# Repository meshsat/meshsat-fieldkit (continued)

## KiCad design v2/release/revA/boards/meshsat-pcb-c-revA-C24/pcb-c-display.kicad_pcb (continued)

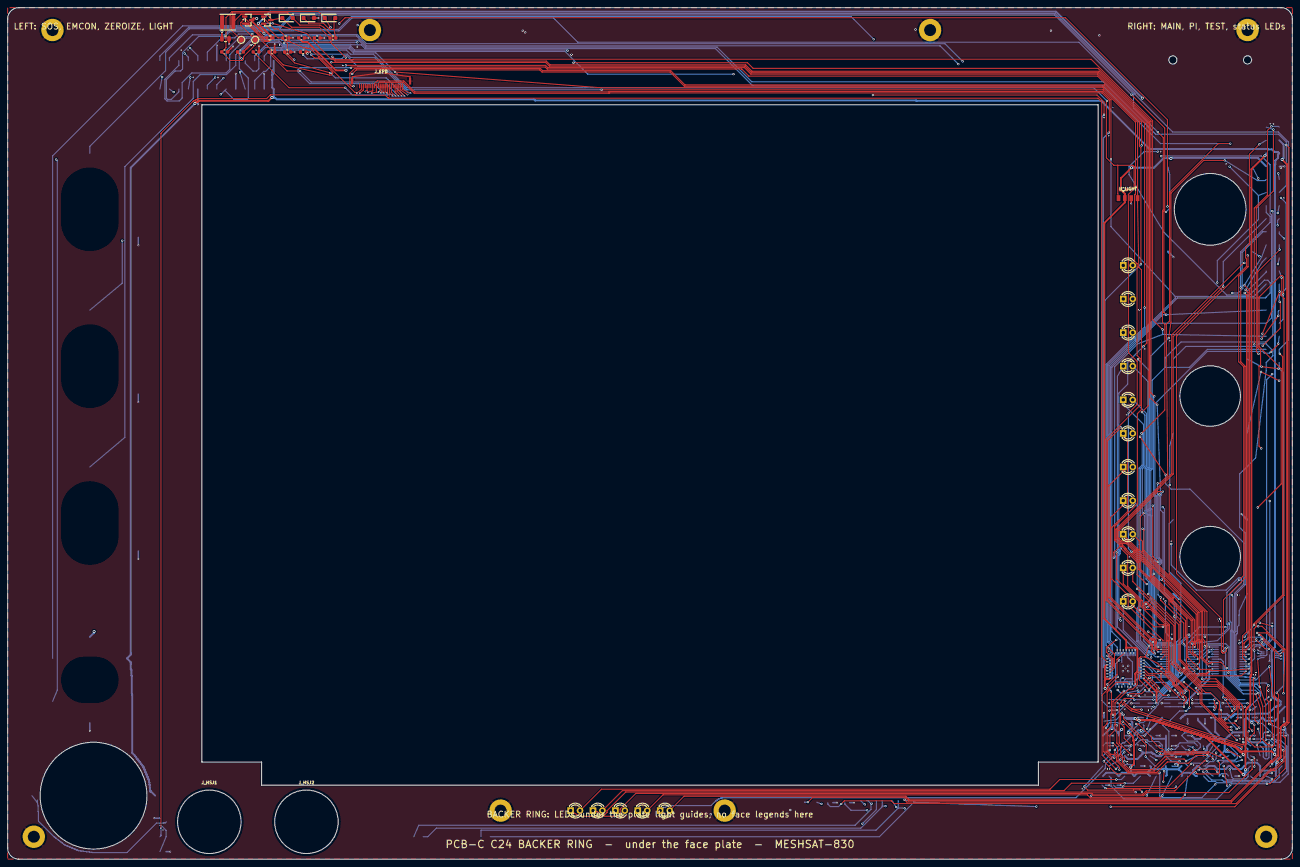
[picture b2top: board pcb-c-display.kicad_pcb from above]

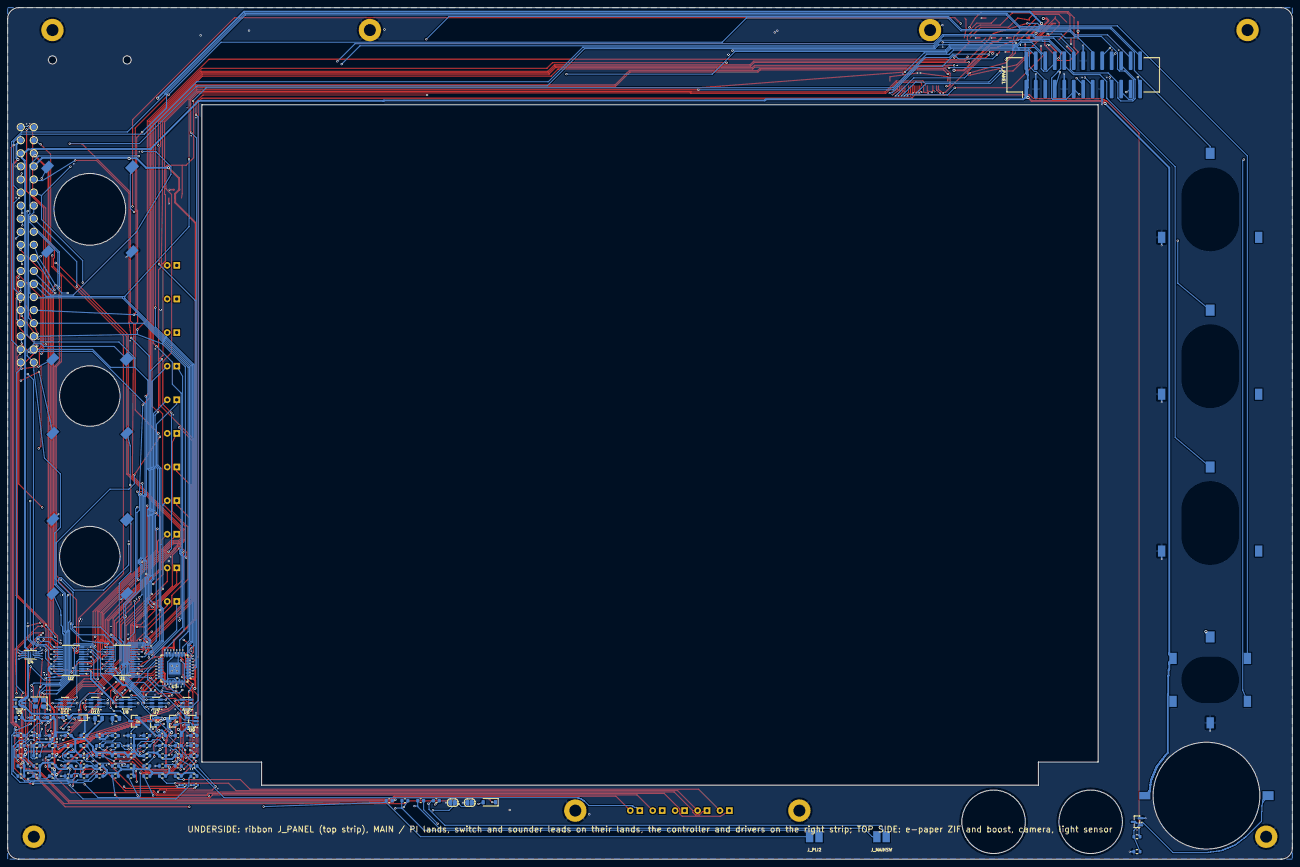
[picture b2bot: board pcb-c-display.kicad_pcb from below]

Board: 4 copper layers, 344.0 x 228.0 mm, 194 parts (135 on the bottom side), 133 nets.

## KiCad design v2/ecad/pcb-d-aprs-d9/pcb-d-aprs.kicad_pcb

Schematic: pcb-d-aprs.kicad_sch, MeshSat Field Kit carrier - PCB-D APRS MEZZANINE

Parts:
C1, C2, C5: 47u 6.3V X5R 1210; C_1210_3225Metric
C3, C9, C17, C24, C25, C33, C40: 10u; C_0805_2012Metric
C4, C6, C11, C15, C16, C39, C49, C50, C51, C52, C53, C54, C55, C56, C57, C62, C63: 100n; C_0603_1608Metric
C7, C8, C12, C18, C19, C20, C21, C22, C23, C28, C29, C30, C31, C32, C34, C35, C36, C37, C38, C41, C42, C46, C47, C48: 1u; C_0603_1608Metric
C10: 4.7u; C_0805_2012Metric
C13, C14: 27p NP0; C_0402_1005Metric
C26, C27: 18p NP0; C_0402_1005Metric
C43: 100p NP0; C_0402_1005Metric
C44, C45: 1n NP0; C_0402_1005Metric
C58, C60: 22p 500V NP0 1206; C_1206_3216Metric
C59: 39p 500V NP0 1206; C_1206_3216Metric
C61: 4.7n; C_0402_1005Metric
D1: SMBJ5.0A; D_SMB
D2: 1N4148W coil flyback; D_SOD-123
FB1: 600R 2A ferrite (the exciter's 1 A transmit pulse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; L_0805_2012Metric
JP1: electret bias headset 1 (close for an electret mi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; SolderJumper-2_P1.3mm_Open_RoundedPad1.0x1.5mm
JP2: electret bias headset 2; SolderJumper-2_P1.3mm_Open_RoundedPad1.0x1.5mm
J_ANT: SMA jack: antenna pigtail to A22's VHF jack J_RF1; SMA_Amphenol_132134_Vertical; LCSC C3174425
J_HARN1: A22 mezzanine harness J_MEZZ1 (IDC 2x8): USB pair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; IDC-Header_2x08_P2.54mm_Vertical_NarrowPad
J_HS1: JST-PH 1x5 socket: headset 1, SPK GND MIC GND PTT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; JST_PH_B5B-PH-K_1x05_P2.00mm_Vertical; LCSC C157993
J_HS2: JST-PH 1x5 socket: headset 2, SPK GND MIC GND PTT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; JST_PH_B5B-PH-K_1x05_P2.00mm_Vertical; LCSC C157993
J_PAIN: U.FL socket: PA drive (coax to the RA30H1317M1 in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; U.FL_Hirose_U.FL-R-SMT-1_Vertical; LCSC C88373
J_PAOUT: SMA jack: PA output (coax from the RA30H1317M1 ou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; SMA_Amphenol_132134_Vertical; LCSC C3174425
J_PWR1: JST-VH socket, 10 A: 5 V from A22 J_MEZZ_PWR1 (be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; JST_VH_B2P-VH_1x02_P3.96mm_Vertical; LCSC C274411
J_USB3: JST-PH 1x4 socket: spare hub port 3, 5V D- D+ GND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; JST_PH_B4B-PH-K_1x04_P2.00mm_Vertical; LCSC C131334
J_VGG: JST-PH 1x2 socket: PA gate bias, VGG GND (the lea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; JST_PH_B2B-PH-K_1x02_P2.00mm_Vertical; LCSC C5251182
K1: Omron G6K-2F-Y 5 VDC DPDT signal relay, T/R; Relay_DPDT_Omron_G6K-2F-Y
L1: 68nH 0805 (LPF, 145 MHz 5th order; values to be v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; L_0805_2012Metric
L2: 68nH 0805 (LPF); L_0805_2012Metric
LED1: green power; LED_0603_1608Metric; LCSC C12624
LED2: amber record; LED_0603_1608Metric; LCSC C2287
LED3: green playback; LED_0603_1608Metric; LCSC C12624
LED4: red transmit; LED_0603_1608Metric; LCSC C2286
LED5: amber PA keyed; LED_0603_1608Metric; LCSC C2287
LED6: green receive (AUDIO_ON low); LED_0603_1608Metric; LCSC C12624
Q1: 2N7002 PA_EN -> H/L low (never tie H/L high); SOT-23; LCSC C8545
Q2: 2N7002 relay coil; SOT-23; LCSC C8545
Q3, Q4, Q5, Q6, Q7, Q8, Q9: 2N7002; SOT-23; LCSC C8545
R1, R43, R44, R51: 2.2k; R_0603_1608Metric
R2, R3, R34, R53: 100k; R_0603_1608Metric
R4, R29, R30, R49, R50, R52: 1k; R_0603_1608Metric
R5, R9, R10, R31, R32, R35, R36, R37, R38, R39, R45, R46, R47, R66, R67, R68, R69, R70, R71, R72, R73, R74, R75, R76, R77, R78, R79: 10k; R_0603_1608Metric
R6, R7, R12, R13, R16, R17, R20, R21: 22; R_0603_1608Metric
R8, R11, R28: 1.5k; R_0603_1608Metric
R14, R15, R18, R19, R22, R23, R24, R25: 15k; R_0603_1608Metric
R26, R27: 33; R_0603_1608Metric
R33, R40, R41: 4.7k; R_0603_1608Metric
R42: 220k; R_0603_1608Metric
R48: 100; R_0603_1608Metric
R54, R56: 27 1% 2010; R_2010_5025Metric
R55: 36 1% 2010; R_2010_5025Metric
TP1: AF_OUT; TestPoint_Pad_D1.5mm
TP2: MIC_SUM; TestPoint_Pad_D1.5mm
TP3: KEY; TestPoint_Pad_D1.5mm
TP4: PA_KEY; TestPoint_Pad_D1.5mm
TP5: +3V3_D8; TestPoint_Pad_D1.5mm
TP6: +5V_D8; TestPoint_Pad_D1.5mm
TP7: VGG_SW; TestPoint_Pad_D1.5mm
TP8: RX_MIX; TestPoint_Pad_D1.5mm
TP9: ZEROIZE_HW; TestPoint_Pad_D1.5mm
TP10: AB_SPARE; TestPoint_Pad_D1.5mm
TP11: SA_TXD; TestPoint_Pad_D1.5mm
TP12: SA_RXD; TestPoint_Pad_D1.5mm
TP13: PTT_SW_n; TestPoint_Pad_D1.5mm
TP14: SA_PD; TestPoint_Pad_D1.5mm
TP15: TX_INHIBIT_n; TestPoint_Pad_D1.5mm
TP16: PA_EN; TestPoint_Pad_D1.5mm
TP17: EXP_SPARE1; TestPoint_Pad_D1.5mm
TP18: EXP_SPARE2; TestPoint_Pad_D1.5mm
TP19: EXP_SPARE3; TestPoint_Pad_D1.5mm
TP20: EXP_SPARE4; TestPoint_Pad_D1.5mm
TP21: EXP_SPARE5; TestPoint_Pad_D1.5mm
TP22: EXP_SPARE6; TestPoint_Pad_D1.5mm
TP23: EXP_SPARE7; TestPoint_Pad_D1.5mm
TP24: EXP_SPARE8; TestPoint_Pad_D1.5mm
U1: TLV75533PDBV 3.3 V 500 mA LDO (1 IN 2 GND 3 EN 4 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; SOT-23-5
U2: NiceRF SA868 VHF 2 W exciter, bench-fitted (caste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; NiceRF_SA868
U3: CP2102N-A02-GQFN28 USB-UART bridge (SAU); QFN-28-1EP_5x5mm_P0.5mm_EP3.35x3.35mm; LCSC C964632
U4: TUSB2046BI four-port USB 2.0 full-speed hub (LQFP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; LQFP-32_7x7mm_P0.8mm
U5: USBLC6-2SC6; SOT-23-6; LCSC C7519
U6: TI PCM2912A USB audio codec (TQFP-32): mono input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; TQFP-32_7x7mm_P0.8mm
U7: TI TPA6132A2 headphone amplifier (QFN-16), receiv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; QFN-16-1EP_3x3mm_P0.5mm_EP1.75x1.75mm
U8: TLV9062IDGK dual op amp (1 OUT1 2 IN1- 3 IN1+ 4 V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; VSSOP-8_3x3mm_P0.65mm
U9: 74LVC1G08 AND (1 A 2 B 3 GND 4 Y 5 VCC): both hea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; SOT-23-5
U10: 74LVC1G08 AND: headsets AND software PTT (RTS); SOT-23-5
U11: 74LVC1G04 inverter (2 A 4 Y): PTT_ANY; SOT-23-5
U12: 74LVC1G08 AND: KEY = PTT_ANY AND TX_INHIBIT_n (th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; SOT-23-5
U13: 74LVC1G04 inverter: KEY -> SA868 PTT (low = trans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; SOT-23-5
U14: 74LVC1G08 AND: PA_KEY = KEY AND PA_EN (A22's PA r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; SOT-23-5
U15: TPS22810DRV; WSON-6-1EP_2x2mm_P0.65mm_EP1x1.6mm
U16: PCA9555PW 0x26: COS, PTT states, KEY, PA_KEY in; 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; TSSOP-24_4.4x7.8mm_P0.65mm
Y1: 6 MHz 3225 (CL 20 pF; C1 = C2 = 27 pF and Rd 1.5k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; Crystal_SMD_3225-4Pin_3.2x2.5mm
Y2: 6 MHz 3225 (codec clock; 18 pF loads, to confirm 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; Crystal_SMD_3225-4Pin_3.2x2.5mm

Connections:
/+3V3: C63.1, J_HARN1.13, R67.2, R69.2, R71.2, R73.2, R75.2, R77.2, R79.2, U16.2 (A1), U16.3 (A2), U16.24 (VDD)
/+3V3_D8: C8.1, C9.1, C15.1, C16.1, C17.1, C51.1, C52.1, C53.1, C54.1, C55.1, C56.1, Q3.1 (G), Q4.1 (G), Q5.1 (G), Q6.1 (G), Q7.1 (G), Q8.1 (G), Q9.1 (G), R1.1, R5.2, R8.2, R9.2, R10.2, R29.1, R30.1, R51.1, R66.2, R68.2, R70.2, R72.2, R74.2, R76.2, R78.2, TP5.1, U1.5 (+3V3_D8), U4.3 (VCC), U4.6 (EEDATA/GANGED), U4.25 (VCC), U4.26 (EXTMEM), U7.6 (G0), U9.5 (+3V3_D8), U10.5 (+3V3_D8), U11.5 (+3V3_D8), U12.5 (+3V3_D8), U13.5 (+3V3_D8), U14.5 (+3V3_D8)
/+5V_D8: C1.1, C2.1, C3.1, C4.1, C7.1, C18.1, C32.1, C33.1, C39.1, C57.1, D1.2 (A2), D2.1 (K), FB1.1, J_PWR1.1, J_USB3.1, K1.1, R38.1, R43.2, R44.2, TP6.1, U1.1 (+5V_D8), U1.3 (+5V_D8), U3.7 (VREGIN), U3.8 (VBUS), U5.5 (VBUS), U6.2 (VBUS), U7.14 (VDD), U8.8 (+5V_D8), U15.6 (VIN)
/+5V_SA: C5.1, C6.1, FB1.2, U2.8 (VBAT)
/AB_SPARE: J_HARN1.16, TP10.1
/AF_DIV: C28.1, R31.2, R32.1
/AF_OUT: R31.1, R35.1, TP1.1, U2.3 (AF_OUT)
/AMP_CPN: C30.2, U7.9 (CPN)
/AMP_CPP: C30.1, U7.11 (CPP)
/AMP_EN: Q9.2 (S), R78.1, U7.13 (EN)
/AMP_HPVDD: C31.1, U7.12 (HPVDD)
/AMP_HPVSS: C29.1, U7.8 (HPVSS)
/AMP_INL_N: C37.1, U7.1 (INL-)
/AMP_INL_P: C35.2, U7.2 (INL+)
/AMP_INR_N: C38.1, U7.4 (INR-)
/AMP_INR_P: C36.2, U7.3 (INR+)
/EXP_INT: J_HARN1.12, U16.1 (~INT)
/EXP_SPARE1: TP17.1, U16.13 (IO1_0)
/EXP_SPARE2: TP18.1, U16.14 (IO1_1)
/EXP_SPARE3: TP19.1, U16.15 (IO1_2)
/EXP_SPARE4: TP20.1, U16.16 (IO1_3)
/EXP_SPARE5: TP21.1, U16.17 (IO1_4)
/EXP_SPARE6: TP22.1, U16.18 (IO1_5)
/EXP_SPARE7: TP23.1, U16.19 (IO1_6)
/EXP_SPARE8: TP24.1, U16.20 (IO1_7)
/HS1_BIAS_R: JP1.2 (B), R43.1
/HS1_MIC: C41.1, C44.1, JP1.1 (A), J_HS1.3
/HS1_MIC_AC: C41.2, R40.1
/HS1_SPK: J_HS1.1, U7.16 (OUTL)
/HS2_BIAS_R: JP2.2 (B), R44.1
/HS2_MIC: C42.1, C45.1, JP2.1 (A), J_HS2.3
/HS2_MIC_AC: C42.2, R41.1
/HS2_SPK: J_HS2.1, U7.5 (OUTR)
/HUB_DM0: R7.2, U4.2 (DM0)
/HUB_DM1: R13.1, U4.11 (DM1)
/HUB_DM2: R17.1, U4.15 (DM2)
/HUB_DM3: R21.1, U4.19 (DM3)
/HUB_DM4: R25.1, U4.23 (DM4)
/HUB_DP0: R6.2, R8.1, U4.1 (DP0)
/HUB_DP1: R12.1, U4.12 (DP1)
/HUB_DP2: R16.1, U4.16 (DP2)
/HUB_DP3: R20.1, U4.20 (DP3)
/HUB_DP4: R24.1, U4.24 (DP4)
/HUB_OVRCUR_n: R9.1, U4.10 (OVRCUR1_n), U4.14 (OVRCUR2_n), U4.18 (OVRCUR3_n), U4.22 (OVRCUR4_n)
/HUB_RST_n: C12.1, R10.1, U4.4 (RESET_n)
/HUB_XTAL1: C13.1, U4.30 (XTAL1), Y1.1
/HUB_XTAL2: R11.2, U4.29 (XTAL2)
/HUB_XTAL2R: C14.1, R11.1, Y1.3
/KEY: Q6.2 (S), R48.1, R49.1, R72.1, TP3.1, U12.4 (KEY), U13.2 (KEY), U14.1 (KEY)
/LED_PA_A: LED5.2 (A), R50.2
/LED_PLAY_A: LED3.2 (A), R30.2
/LED_PLAY_K: LED3.1 (K), U6.32 (PLAY)
/LED_PWR_A: LED1.2 (A), R1.2
/LED_REC_A: LED2.2 (A), R29.2
/LED_REC_K: LED2.1 (K), U6.31 (REC)
/LED_RX_A: LED6.2 (A), R51.2
/LED_TX_A: LED4.2 (A), R49.2
/MICAMP_AC: C46.2, R45.1
/MICAMP_IN_N: C43.2, R40.2, R41.2, R42.2, U8.2 (MICAMP_IN_N)
/MICAMP_OUT: C43.1, C46.1, R42.1, U8.1 (MICAMP_OUT)
/MIC_IN: C48.2, U2.18 (MIC_IN)
/MIC_SUM: C48.1, R45.2, R46.2, R47.1, TP2.1
/MMUTE: R33.2, R34.1, U6.30 (MMUTE)
/OPB_OUT: U8.6 (OPB_OUT), U8.7 (OPB_OUT)
/PA_EN: J_HARN1.9, Q1.1 (G), R3.1, TP16.1, U14.2 (PA_EN)
/PA_KEY: Q7.2 (S), R50.1, R52.1, R74.1, TP4.1, U14.4 (PA_KEY), U15.5 (EN/UVLO)
/PCM_L_AC: C34.2, R36.1
/PCM_R_AC: C47.2, R46.1
/PCM_VCCA: C20.1, U6.15 (VCCA)
/PCM_VCCL: C21.1, U6.19 (VCCL)
/PCM_VCCP: C23.1, U6.26 (VCCP)
/PCM_VCCR: C22.1, U6.21 (VCCR)
/PCM_VCOM1: C24.1, U6.11 (VCOM1)
/PCM_VCOM2: C25.1, U6.12 (VCOM2)
/PCM_VDD: C19.1, R28.2, U6.5 (VDD), U6.27 (TEST1)
/PCM_VIN: C28.2, U6.16 (VIN)
/PCM_VOUTL: C34.1, U6.18 (VOUTL)
/PCM_VOUTR: C47.1, U6.22 (VOUTR)
/PCM_XTI: C26.1, U6.8 (XTI), Y2.1
/PCM_XTO: C27.1, U6.7 (XTO), Y2.3
/PTT_ANY: U11.4 (PTT_ANY), U12.1 (PTT_ANY)
/PTT_ANY_n: U10.4 (PTT_ANY_n), U11.2 (PTT_ANY_n)
/PTT_HS1_n: C49.1, J_HS1.5, Q4.2 (S), R68.1, U9.1 (PTT_HS1_n)
/PTT_HS2_n: C50.1, J_HS2.5, Q5.2 (S), R70.1, U9.2 (PTT_HS2_n)
/PTT_HS_n: U9.4 (PTT_HS_n), U10.1 (PTT_HS_n)
/PTT_SW_n: R5.1, TP13.1, U3.24 (RTS), U10.2 (PTT_SW_n)
/RF_ANT: J_ANT.1 (In), K1.6
/RF_DRV: J_PAIN.1 (In), R56.2
/RF_LPF_M: C59.1, L1.2, L2.1
/RF_LPF_OUT: C60.1, K1.5, L2.2
/RF_PAD_IN: K1.4, R54.1
/RF_PAD_M: R54.2, R55.1, R56.1
/RF_PAOUT: C58.1, J_PAOUT.1 (In), L1.1
/RF_RX: K1.2, K1.7
/RF_SA: K1.3, U2.12 (ANT)
/RLY_DRV: Q2.1 (G), R52.2, R53.1
/RLY_K: D2.2 (A), K1.8, Q2.3 (D)
/RX_MIX: C35.1, C36.1, R35.2, R36.2, R37.1, TP8.1
/SAU_3V3: C10.1, C11.1, R4.2, U3.6 (VDD)
/SAU_RST: R4.1, U3.9 (RSTb)
/SA_AUDIO_ON_n: LED6.1 (K), Q3.2 (S), R66.1, U2.1 (AUDIO_ON_n)
/SA_HL: Q1.3 (D), U2.7 (H/L)
/SA_PD: Q8.2 (S), R76.1, TP14.1, U2.6 (PD)
/SA_PTT_n: U2.5 (PTT_n), U13.4 (SA_PTT_n)
/SA_RXD: TP12.1, U2.16 (RXD), U3.26 (TXD)
/SA_TXD: TP11.1, U2.17 (TXD), U3.25 (RXD)
/SCL: J_HARN1.11, U16.22 (SCL)
/SDA: J_HARN1.10, U16.23 (SDA)
/TR_APRS: J_HARN1.7, R48.2
/TX_INHIBIT_n: J_HARN1.8, R2.1, TP15.1, U12.2 (TX_INHIBIT_n)
/USB1_N: R13.2, R15.1, R27.1
/USB1_NR: R27.2, U6.3 (D-)
/USB1_P: R12.2, R14.1, R26.1
/USB1_PR: R26.2, R28.1, U6.4 (D+)
/USB2_N: R17.2, R19.1, U3.5 (D-)
/USB2_P: R16.2, R18.1, U3.4 (D+)
/USB3_N: J_USB3.2, R21.2, R23.1
/USB3_P: J_USB3.3, R20.2, R22.1
/USB_D8_N: J_HARN1.2, R7.1, U5.3 (I/O2), U5.4 (I/O2)
/USB_D8_P: J_HARN1.1, R6.1, U5.1 (I/O1), U5.6 (I/O1)
/VGG_CT: C61.1, U15.3 (CT)
/VGG_SW: C62.1, J_VGG.1, TP7.1, U15.1 (VOUT)
/VREF: C40.1, R38.2, R39.1, U8.3 (VREF), U8.5 (VREF)
/X_AMP_EN: Q9.3 (D), R79.1, U16.10 (IO0_6)
/X_COS_n: Q3.3 (D), R67.1, U16.4 (IO0_0)
/X_KEY: Q6.3 (D), R73.1, U16.7 (IO0_3)
/X_MMUTE: R33.1, U16.11 (IO0_7)
/X_PA_KEY: Q7.3 (D), R75.1, U16.8 (IO0_4)
/X_PTT_HS1_n: Q4.3 (D), R69.1, U16.5 (IO0_1)
/X_PTT_HS2_n: Q5.3 (D), R71.1, U16.6 (IO0_2)
/X_SA_PD: Q8.3 (D), R77.1, U16.9 (IO0_5)
/ZEROIZE_HW: J_HARN1.15, TP9.1
GND: C1.2, C2.2, C3.2, C4.2, C5.2, C6.2, C7.2, C8.2, C9.2, C10.2, C11.2, C12.2, C13.2, C14.2, C15.2, C16.2, C17.2, C18.2, C19.2, C20.2, C21.2, C22.2, C23.2, C24.2, C25.2, C26.2, C27.2, C29.2, C31.2, C32.2, C33.2, C37.2, C38.2, C39.2, C40.2, C44.2, C45.2, C49.2, C50.2, C51.2, C52.2, C53.2, C54.2, C55.2, C56.2, C57.2, C58.2, C59.2, C60.2, C61.2, C62.2, C63.2, D1.1 (A1), J_ANT.2 (Ext), J_HARN1.3, J_HARN1.4, J_HARN1.5, J_HARN1.6, J_HARN1.14, J_HS1.2, J_HS1.4, J_HS2.2, J_HS2.4, J_PAIN.2 (Ext), J_PAOUT.2 (Ext), J_PWR1.2, J_USB3.4, J_VGG.2, LED1.1 (K), LED4.1 (K), LED5.1 (K), Q1.2 (S), Q2.2 (S), R2.2, R3.2, R14.2, R15.2, R18.2, R19.2, R22.2, R23.2, R24.2, R25.2, R32.2, R34.2, R37.2, R39.2, R47.2, R53.2, R55.2, U1.2 (GND), U2.9 (GND), U2.10 (GND), U3.3 (GND), U3.29 (GND), U4.7 (GND), U4.8 (BUSPWR), U4.27 (TSTPLL/48MCLK), U4.28 (GND), U4.31 (TSTMODE), U5.2 (GND), U6.1 (BGND), U6.6 (DGND), U6.13 (AGND), U6.20 (HGND), U6.23 (MAMP), U6.24 (POWER), U6.25 (PGND), U6.28 (TEST0), U7.7 (G1), U7.10 (PGND), U7.15 (SGND), U7.17 (PAD), U8.4 (GND), U9.3 (GND), U10.3 (GND), U11.3 (GND), U12.3 (GND), U13.3 (GND), U14.3 (GND), U15.4 (GND), U15.7 (GND), U16.12 (VSS), U16.21 (A0), Y1.2 (G), Y1.4 (G), Y2.2 (G), Y2.4 (G)

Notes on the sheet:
PCB-D APRS MEZZANINE D12
HARNESS, 5 V ENTRY, 3.3 V LDO, EXCITER SUPPLY | SA868 EXCITER, UART BRIDGE, T/R RELAY, 10 dB PAD, LPF, PA LEADS, GATE BIAS SWITCH
HARNESS, 5 V ENTRY, 3.3 V LDO, EXCITER SUPPLY
SA868 EXCITER, UART BRIDGE, T/R RELAY, 10 dB PAD, LPF, PA LEADS, GATE BIAS SWITCH
page 1 of 5 MeshSat field kit V2, CERN-OHL-S-2.0 PROTOTYPE, nothing built 2026-09-16
A22 mezzanine harness J_MEZZ1
JST-VH socket
47u 6.3V
600R 2A
TLV75533PDBV 3.3 V 500 mA LDO
NiceRF SA868 VHF 2 W exciter
2N7002 PA_EN -> H/L low
CP2102N-A02-GQFN28 USB-UART bridge
Omron G6K-2F-Y 5 VDC DPDT signal r..
27 1%
68nH 0805
U.FL socket
SMA jack
22p 500V
39p 500V
p4,5
p3,5
SA868 EXCITER, UART BRIDGE, T/R RELAY, 10 dB PAD, LPF, PA LEADS, GATE BIAS SWITCH | USB HUB TUSB2046B, PORT TERMINATIONS, SPARE PORT
SA868 EXCITER, UART BRIDGE, T/R RELAY, 10 dB PAD, LPF, PA LEADS, GATE BIAS SWITCH (continued)
USB HUB TUSB2046B, PORT TERMINATIONS, SPARE PORT
page 2 of 5 MeshSat field kit V2, CERN-OHL-S-2.0 PROTOTYPE, nothing built 2026-09-16
JST-PH 1x2 socket
TUSB2046BI four-port USB 2.0 full-..
6 MHz 3225
JST-PH 1x4 socket
USB AUDIO CODEC PCM2912A, HEADPHONE AMPLIFIER, MIC PREAMP, HEADSET LEADS
page 3 of 5 MeshSat field kit V2, CERN-OHL-S-2.0 PROTOTYPE, nothing built 2026-09-16
TI PCM2912A USB audio codec
decoupling of U6
TI TPA6132A2 headphone amplifier
TLV9062IDGK dual op amp
p1,5
USB AUDIO CODEC PCM2912A, HEADPHONE AMPLIFIER, MIC PREAMP, HEADSET LEADS | PTT AND EMCON LOGIC, PTT MIRROR, LEDS, EXPANDER 0x26 WITH LEVEL STAGES, TEST POINTS, FLAGS
USB AUDIO CODEC PCM2912A, HEADPHONE AMPLIFIER, MIC PREAMP, HEADSET LEADS (continued)
PTT AND EMCON LOGIC, PTT MIRROR, LEDS, EXPANDER 0x26 WITH LEVEL STAGES, TEST POINTS, FLAGS

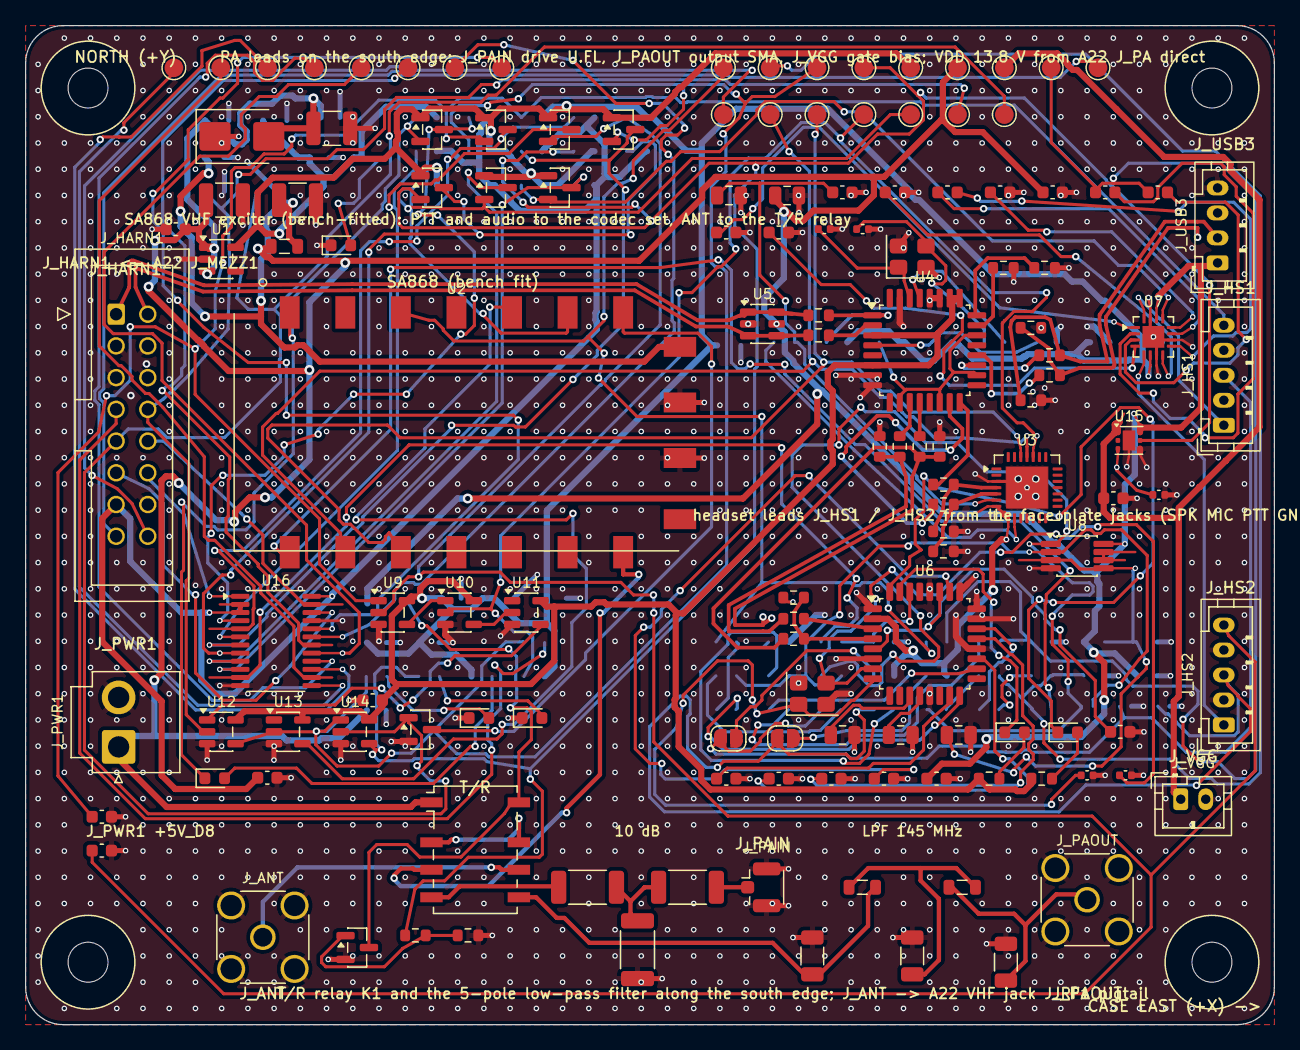
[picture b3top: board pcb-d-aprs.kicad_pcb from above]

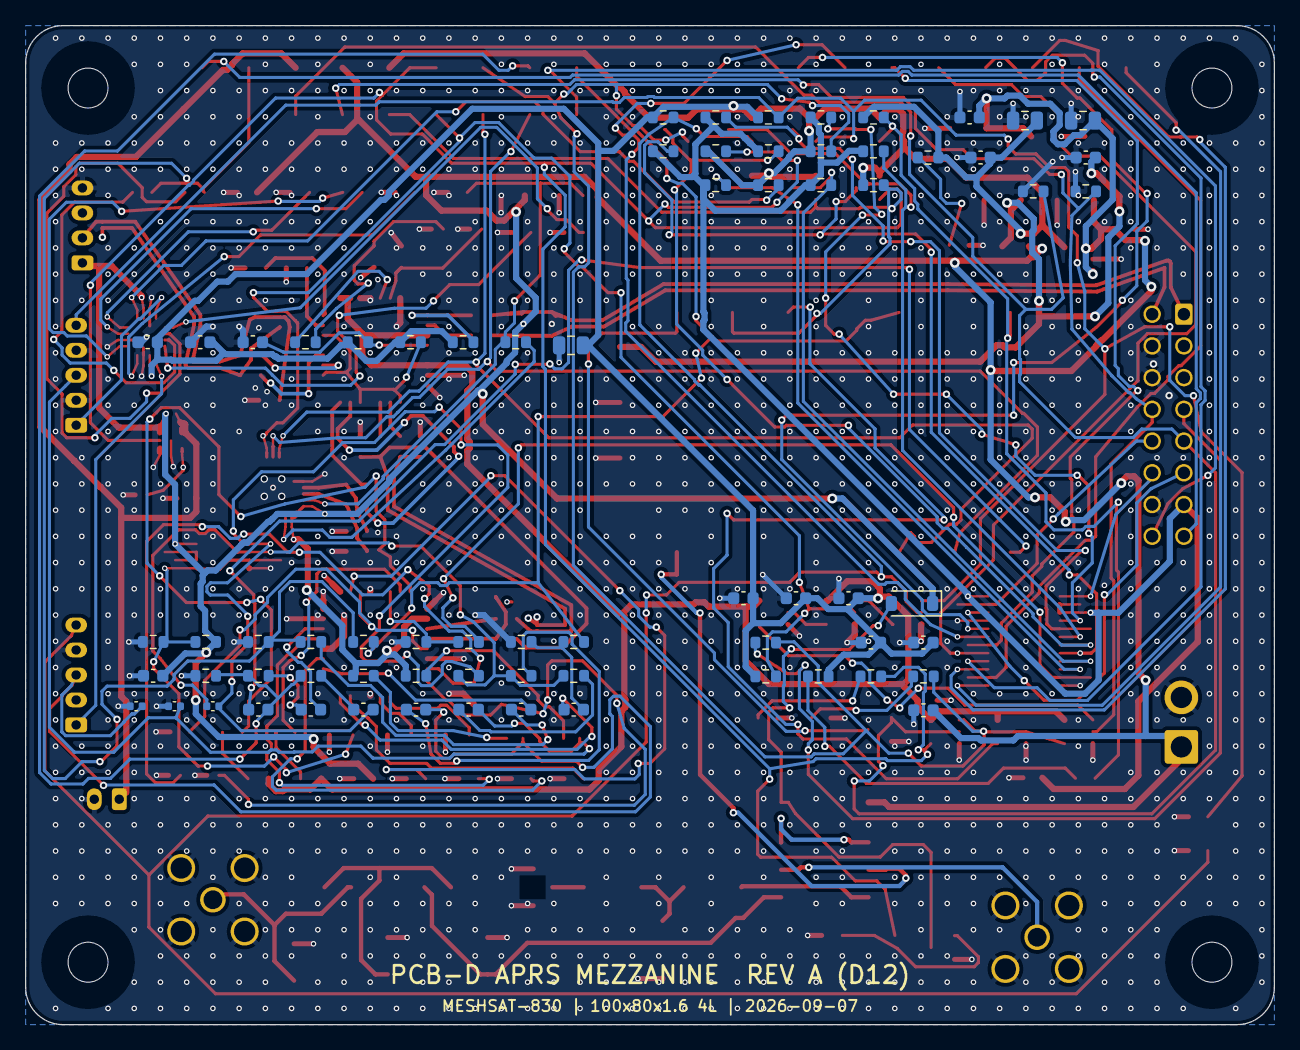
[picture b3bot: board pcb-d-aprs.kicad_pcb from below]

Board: 4 copper layers, 100.0 x 80.0 mm, 211 parts (71 on the bottom side), 133 nets.

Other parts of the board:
H1, H2, H3, H4: M3 standoff on A22 (5/95, +-35); MountingHole_3.2mm_M3
